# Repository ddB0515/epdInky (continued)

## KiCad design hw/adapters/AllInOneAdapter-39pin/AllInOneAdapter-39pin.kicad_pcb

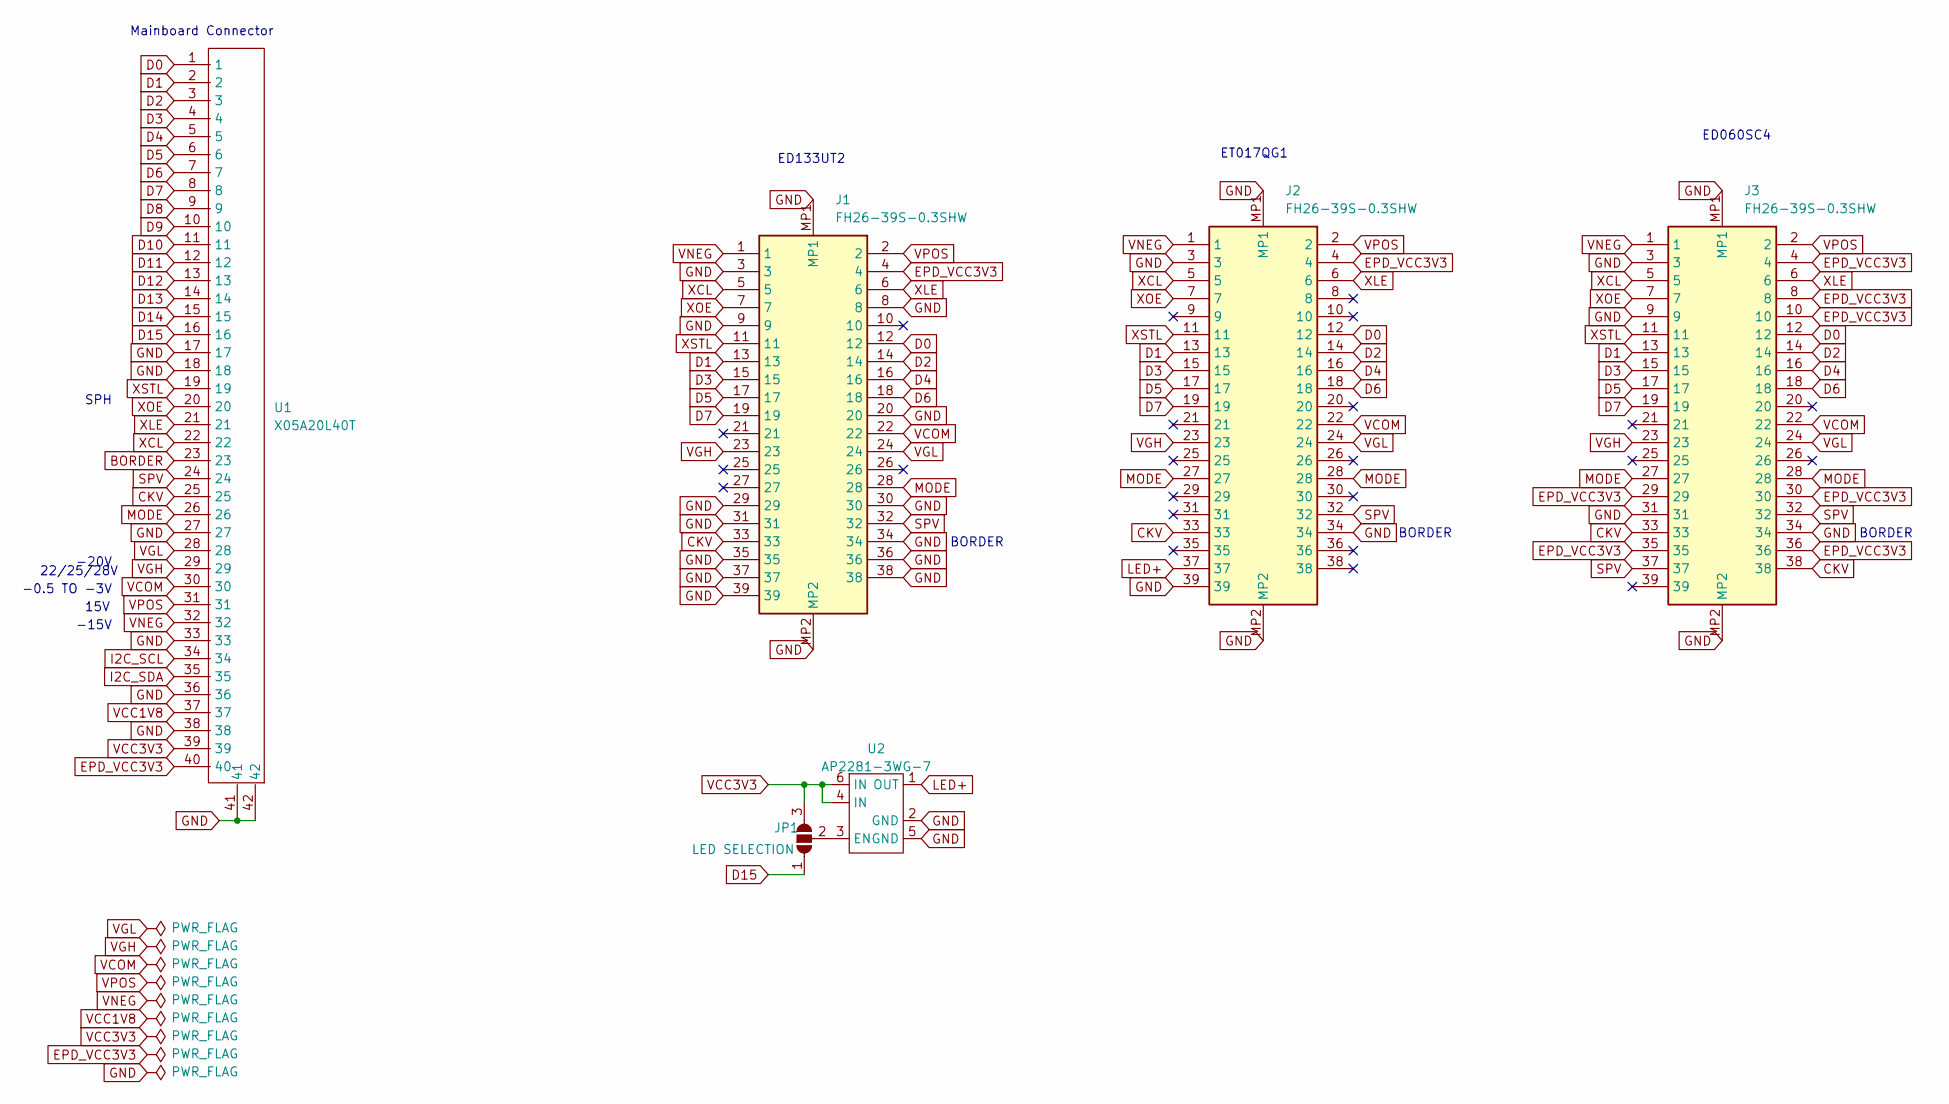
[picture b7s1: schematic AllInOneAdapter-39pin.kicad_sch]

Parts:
J1, J2, J3: FH26-39S-0.3SHW; FH2639S03SHW; Mouser Part Number 798-FH2639S0.3SHW05
JP1: LED SELECTION; SolderJumper-3_P1.3mm_Open_RoundedPad1.0x1.5mm
U1: X05A20L40T; X05A20L40T-2
U2: AP2281-3WG-7; SOT26

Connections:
BORDER: U1.23
CKV: J1.33, J2.33, J3.33, J3.38, U1.25
D0: J1.12, J2.12, J3.12, U1.1
D1: J1.13, J2.13, J3.13, U1.2
D2: J1.14, J2.14, J3.14, U1.3
D3: J1.15, J2.15, J3.15, U1.4
D4: J1.16, J2.16, J3.16, U1.5
D5: J1.17, J2.17, J3.17, U1.6
D6: J1.18, J2.18, J3.18, U1.7
D7: J1.19, J2.19, J3.19, U1.8
D8: U1.9
D9: U1.10
D10: U1.11
D11: U1.12
D12: U1.13
D13: U1.14
D14: U1.15
D15: JP1.1 (A), U1.16
EPD_VCC3V3: J1.4, J2.4, J3.4, J3.8, J3.10, J3.29, J3.30, J3.35, J3.36, U1.40
GND: J1.3, J1.8, J1.9, J1.20, J1.29, J1.30, J1.31, J1.34, J1.35, J1.36, J1.37, J1.38, J1.39, J1.MP1, J1.MP2, J2.3, J2.34, J2.39, J2.MP1, J2.MP2, J3.3, J3.9, J3.31, J3.34, J3.MP1, J3.MP2, U1.17, U1.18, U1.27, U1.33, U1.36, U1.38, U1.41, U1.42, U2.2 (GND), U2.5 (GND)
I2C_SCL: U1.34
I2C_SDA: U1.35
LED+: J2.37, U2.1 (OUT)
MODE: J1.28, J2.27, J2.28, J3.27, J3.28, U1.26
unnamed: JP1.2 (C), U2.3 (EN)
SPV: J1.32, J2.32, J3.32, J3.37, U1.24
VCC1V8: U1.37
VCC3V3: JP1.3 (B), U1.39, U2.4 (IN), U2.6 (IN)
VCOM: J1.22, J2.22, J3.22, U1.30
VGH: J1.23, J2.23, J3.23, U1.29
VGL: J1.24, J2.24, J3.24, U1.28
VNEG: J1.1, J2.1, J3.1, U1.32
VPOS: J1.2, J2.2, J3.2, U1.31
XCL: J1.5, J2.5, J3.5, U1.22
XLE: J1.6, J2.6, J3.6, U1.21
XOE: J1.7, J2.7, J3.7, U1.20
XSTL: J1.11, J2.11, J3.11, U1.19

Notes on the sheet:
-20V
BORDER
SPH
22/25/28V
15V
ET017QG1
-15V
ED133UT2
Mainboard Connector
ED060SC4
-0.5 TO -3V

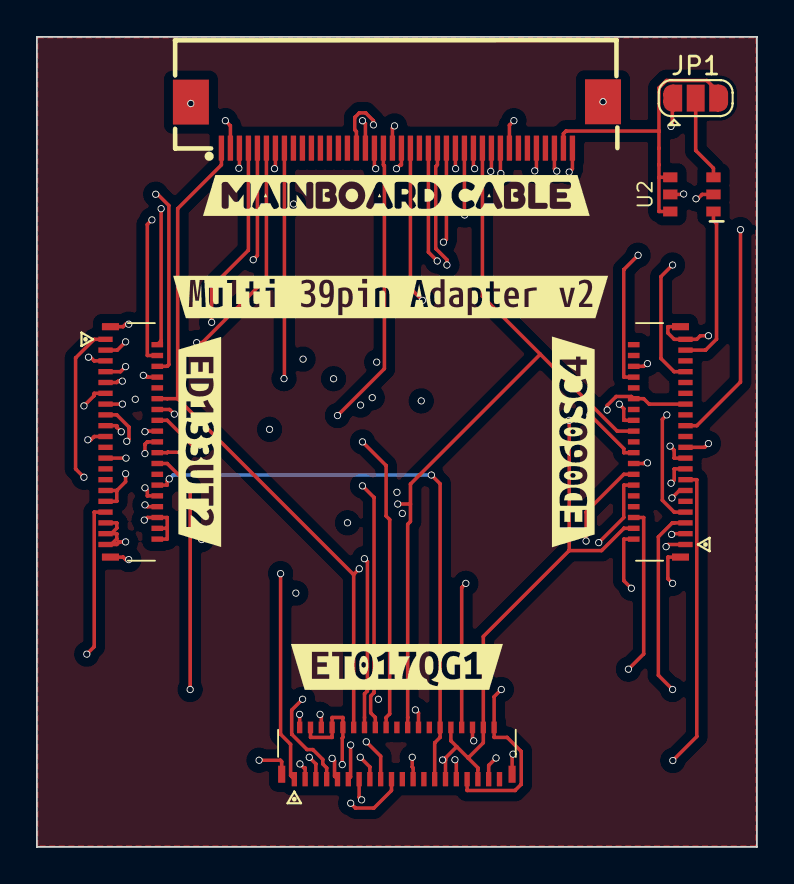
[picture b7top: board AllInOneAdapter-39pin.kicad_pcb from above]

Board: 4 copper layers, 40.0 x 45.0 mm, 11 parts (0 on the bottom side), 26 nets.

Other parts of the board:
kibuzzard-679CBA1D: G***; kibuzzard-679CBA1D
kibuzzard-679CBA3C: G***; kibuzzard-679CBA3C
kibuzzard-679CBA31: G***; kibuzzard-679CBA31
kibuzzard-679CBA36: G***; kibuzzard-679CBA36
kibuzzard-68373226: G***; kibuzzard-68373226

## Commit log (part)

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2026-04-29 initial A260 mipi_demo
2026-04-29 added demo images
2026-04-29 Matrix Editor initial commit example
2026-04-30 Added Basic Demo example
2026-05-07 added calendar demo and some fixes
2026-05-07 added schematic pdf
